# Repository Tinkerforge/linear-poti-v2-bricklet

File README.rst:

Linear Poti Bricklet 2.0
========================

This repository contains the firmware source code and the hardware design
files. The documentation generator configs can be found at
https://github.com/Tinkerforge/generators

Repository Content
------------------

software/:
 * examples/: Examples for all supported languages
 * build/: Compiled files
 * src/: Source code of firmware
 * Makefile: Makefile to build project

hardware/:
 * Contains KiCad project files and additionally schematics as PDF

datasheets/:
 * Contains datasheets for sensors and complex ICs that are used

Hardware
--------

The hardware is designed with the open source EDA Suite KiCad
(http://www.kicad.org). Before you are able to open the files,
you have to install the Tinkerforge kicad-libraries
(https://github.com/Tinkerforge/kicad-libraries). You can either clone
them directly in hardware/ or clone them in a separate folder and
symlink them into hardware/
(ln -s kicad_path/kicad-libraries project_path/hardware). After that you
can open the .pro file in hardware/ with KiCad and from there view and
modify the schematics and the PCB layout.

Software
--------

If you want to do your own Brick/Bricklet firmware development we highly
recommend that you use our build environment setup script and read the
tutorial (https://www.tinkerforge.com/en/doc/Tutorials/Tutorial_Build_Environment/Tutorial.html).

To compile the C code we recommend you to install the newest GNU Arm Embedded
Toolchain (https://launchpad.net/gcc-arm-embedded/+download).
You also need to install bricklib2 (https://github.com/Tinkerforge/bricklib2).

You can either clone it directly in software/src/ or clone it in a
separate folder and symlink it into software/src/
(ln -s bricklib_path/bricklib2 project_path/software/src/). Finally make sure to
have CMake installed (http://www.cmake.org/cmake/resources/software.html).

After that you can build the firmware by invoking make in software/.
The firmware (.zbin) can then be found in software/build/ and uploaded
with brickv (click button "Flashing" on start screen).

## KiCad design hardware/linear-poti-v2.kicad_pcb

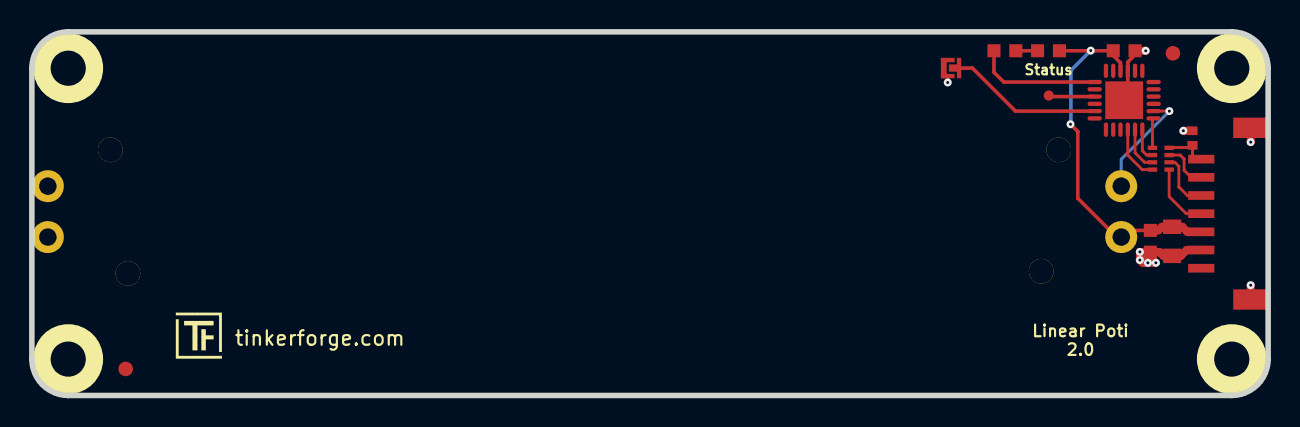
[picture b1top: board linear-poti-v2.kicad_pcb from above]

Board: 2 copper layers, 85.0 x 25.0 mm, 21 parts (0 on the bottom side), 15 nets.

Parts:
C1: 220pF; C0402F
C3: 10uF; C0805
C4: 1uF; C0603F
C5: 100nF; C0603F
D1: blue; D0603F
Fiducial_Mark: VAL**; Fiducial_Mark
Fiducial_Mark#2: VAL**; Fiducial_Mark
P1: CON-SENSOR2
P2: DEBUG; DEBUG_PAD
P3: BOOT; SolderJumper
R3: 1k; R0603F
RP1: 82; 4X0402
RV1: F6005N
Ref**: Val**; Logo_31x31
U1: XMC1100; QFN24-4x4mm-0.5mm
U3, U4, U5, U6: DRILL; DRILL_NP
VAL: CE_5mm
VAL#2: WEEE_7mm

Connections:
GND: C1.2, C3.2, C4.2, C5.2, P1.2, P1.EP, P3.1, RV1.3, U1.9, U1.EXP
IN_1: RV1.2, U1.2
unnamed: C1.1, P1.7, RP1.4
unnamed: D1.2, R3.2
unnamed: P1.4, RP1.1
unnamed: P1.5, RP1.2
unnamed: P1.6, RP1.3
unnamed: P2.1, U1.15
unnamed: P3.2, U1.17
unnamed: R3.1, U1.13
S-CLK: RP1.7, U1.23
S-CS: RP1.8, U1.22
S-MISO: RP1.5, U1.1
S-MOSI: RP1.6, U1.24
VCC: C3.1, C4.1, C5.1, D1.1, P1.3, RV1.1, U1.10

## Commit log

2018-06-22 Add schematic
2018-06-22 Change some pins
2018-06-22 Add layout
2018-06-22 Fix page settings
2018-06-28 Fix readme
2018-06-28 Add .gitignore
2018-06-28 hardware: Fix LibDir
2018-07-04 Fix pin of IN_1
2018-07-11 Fix origin
2018-07-25 Add auto-generated stub firmware
2019-01-17 remove faulty poti connection, drc
2019-02-19 Add and implement Poti API/driver
2019-02-22 changed processor to XMC1100
2019-03-28 mqtt: Fix whitespace.
2019-03-28 Add examples.
2019-04-30 Turn logging off
2019-05-09 add symlib and schematic
2019-05-15 add 3d files
2019-05-20 Update auto-generated rust example
2019-05-20 Release Bricklet
2019-05-20 rust: Use merged imports again.
2019-05-29 Increase version for new release (changes in bricklib2)
2019-05-29 Add rev to changelog
2019-08-22 c: Adapt to bindings changes
2020-01-13 examples: Use python3 input instead of python2 raw_input.
2020-01-13 examples: mqtt: Remove trailing whitespace.
2020-08-19 Add uc examples.
2020-08-25 uc: Fix whitespace
2020-08-27 uc: Fix warnings.
2020-08-31 uc: Use fixed-with placeholders in format strings.
2020-09-02 uc: Add example driver note.
2021-10-25 Update KiCad link
    https://www.kicad.org/blog/2021/10/Avoid-links-to-former-kicad-domain/
2022-04-19 examples: uc: Rename TF_HalContext to TF_HAL.
2022-04-27 uc: Adapt to bindings changes
2022-05-10 Update examples
2022-05-10 go: Fix format string
2022-07-06 Add license files.
2022-09-15 labview: Add examples
2025-10-04 Fix compatibility with new Docker build image (GCC 14.2.1)

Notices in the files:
hardware/linear-poti-v2.kicad_pcb:
Licensed under CERN OHL v.1.1
Copyright (©) 2018, L.Lauer
Copyright Tinkerforge GmbH 2018.
This documentation describes Open Hardware and is licensed under the
CERN OHL v. 1.1.
